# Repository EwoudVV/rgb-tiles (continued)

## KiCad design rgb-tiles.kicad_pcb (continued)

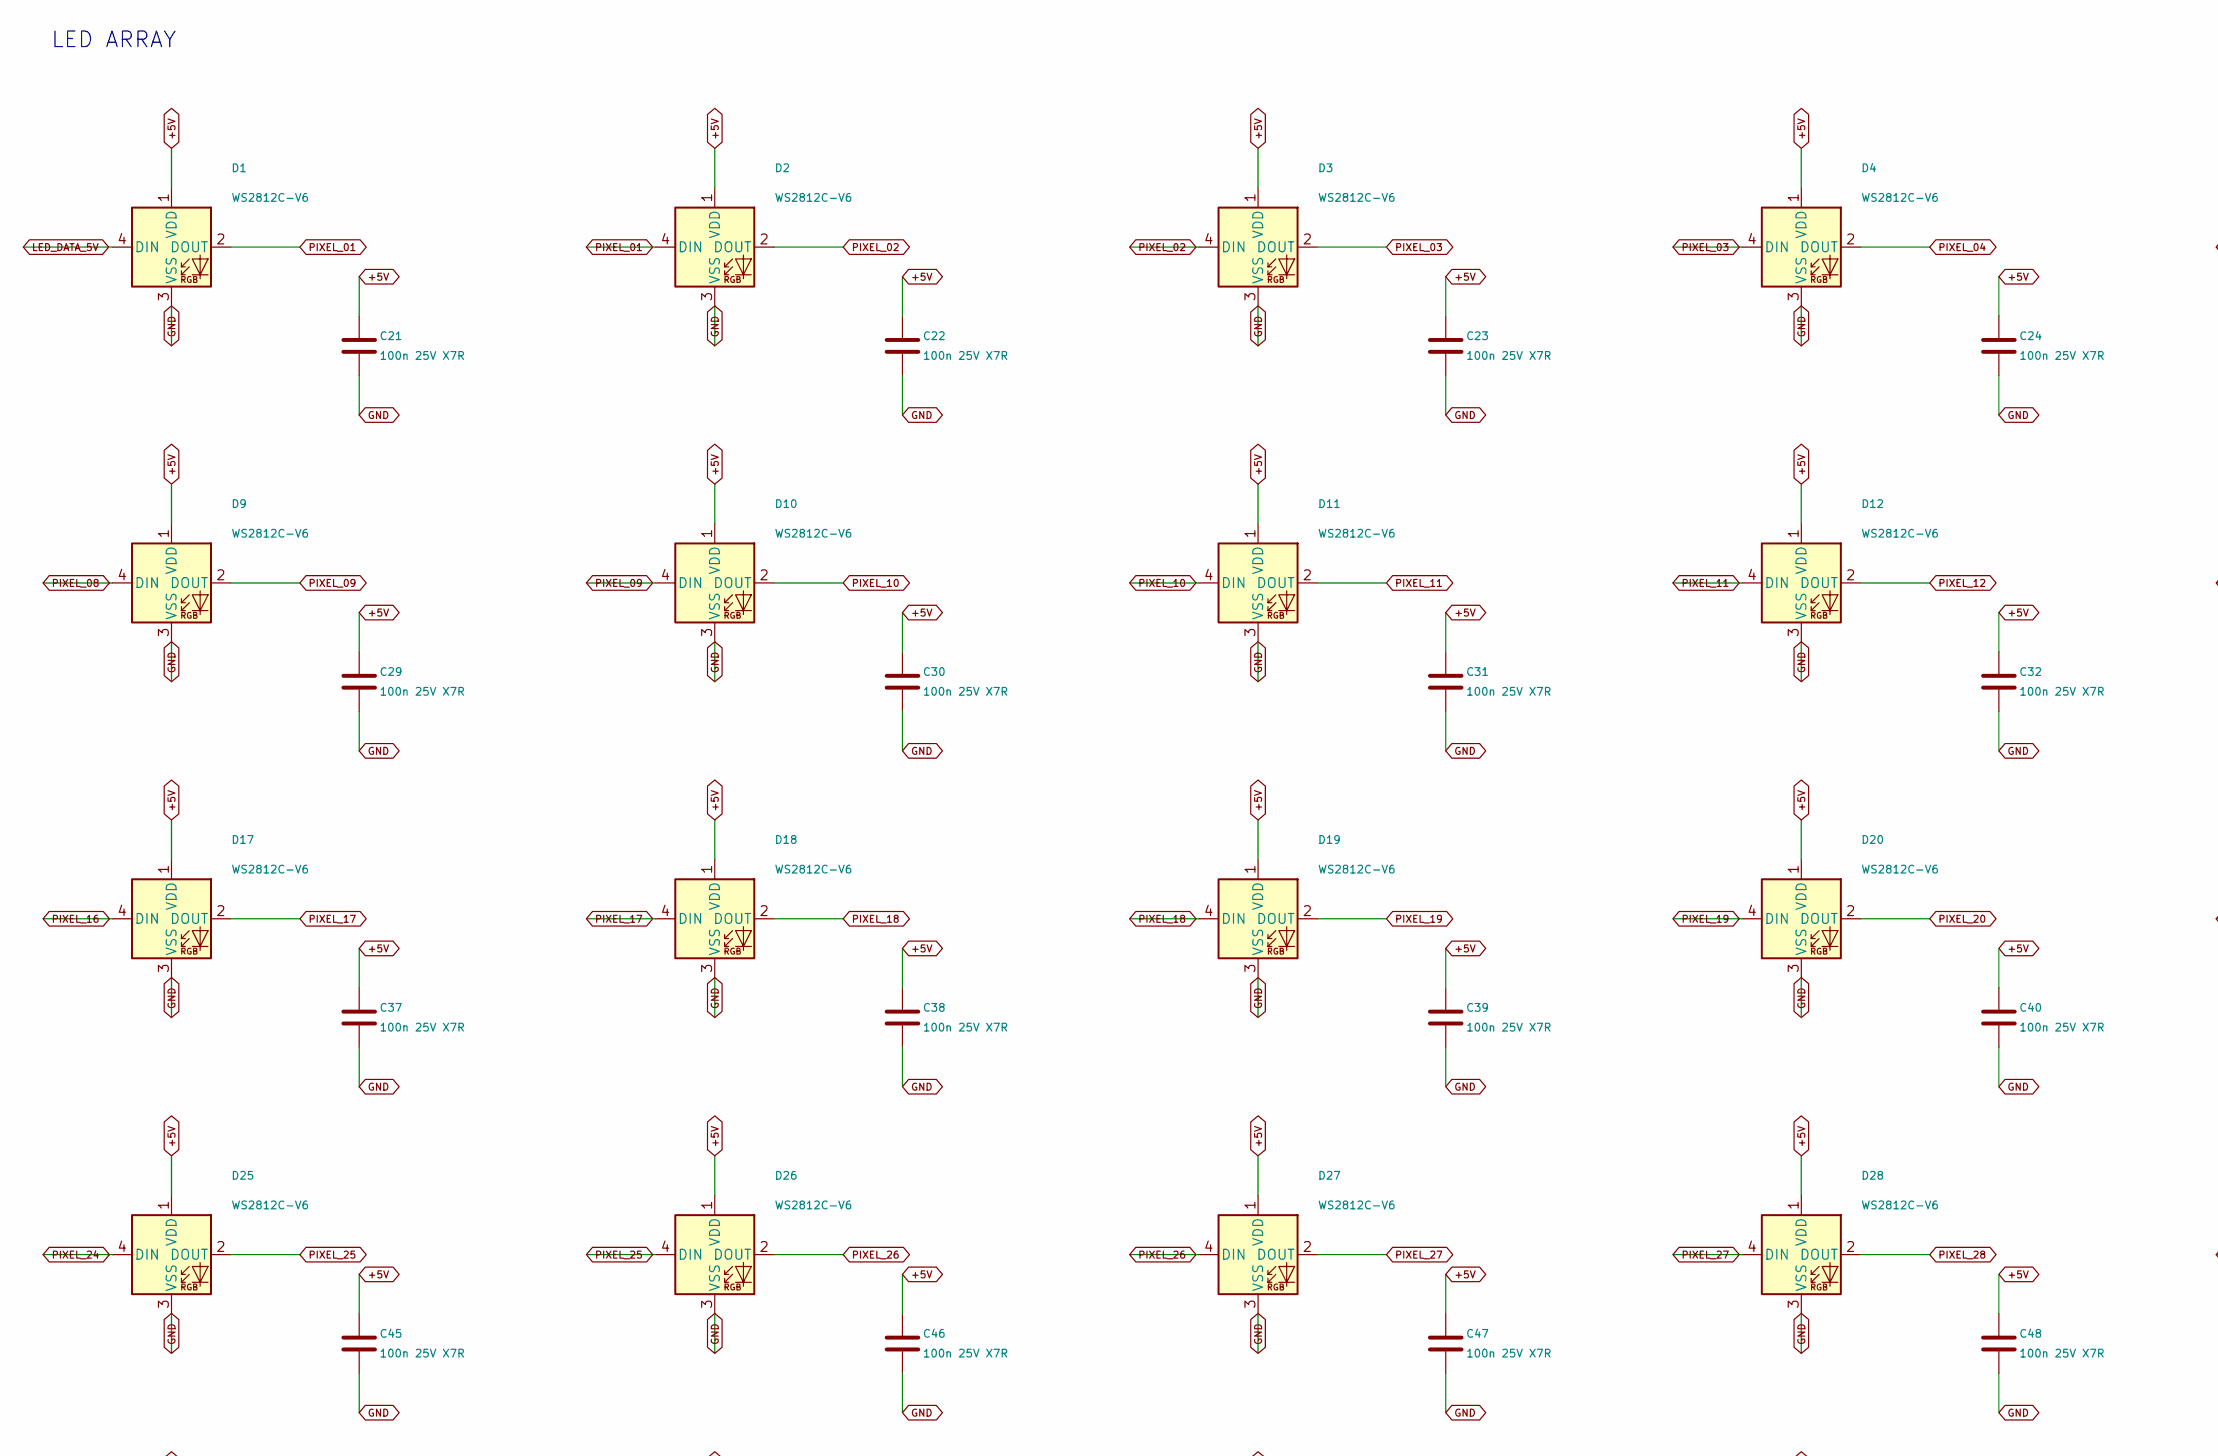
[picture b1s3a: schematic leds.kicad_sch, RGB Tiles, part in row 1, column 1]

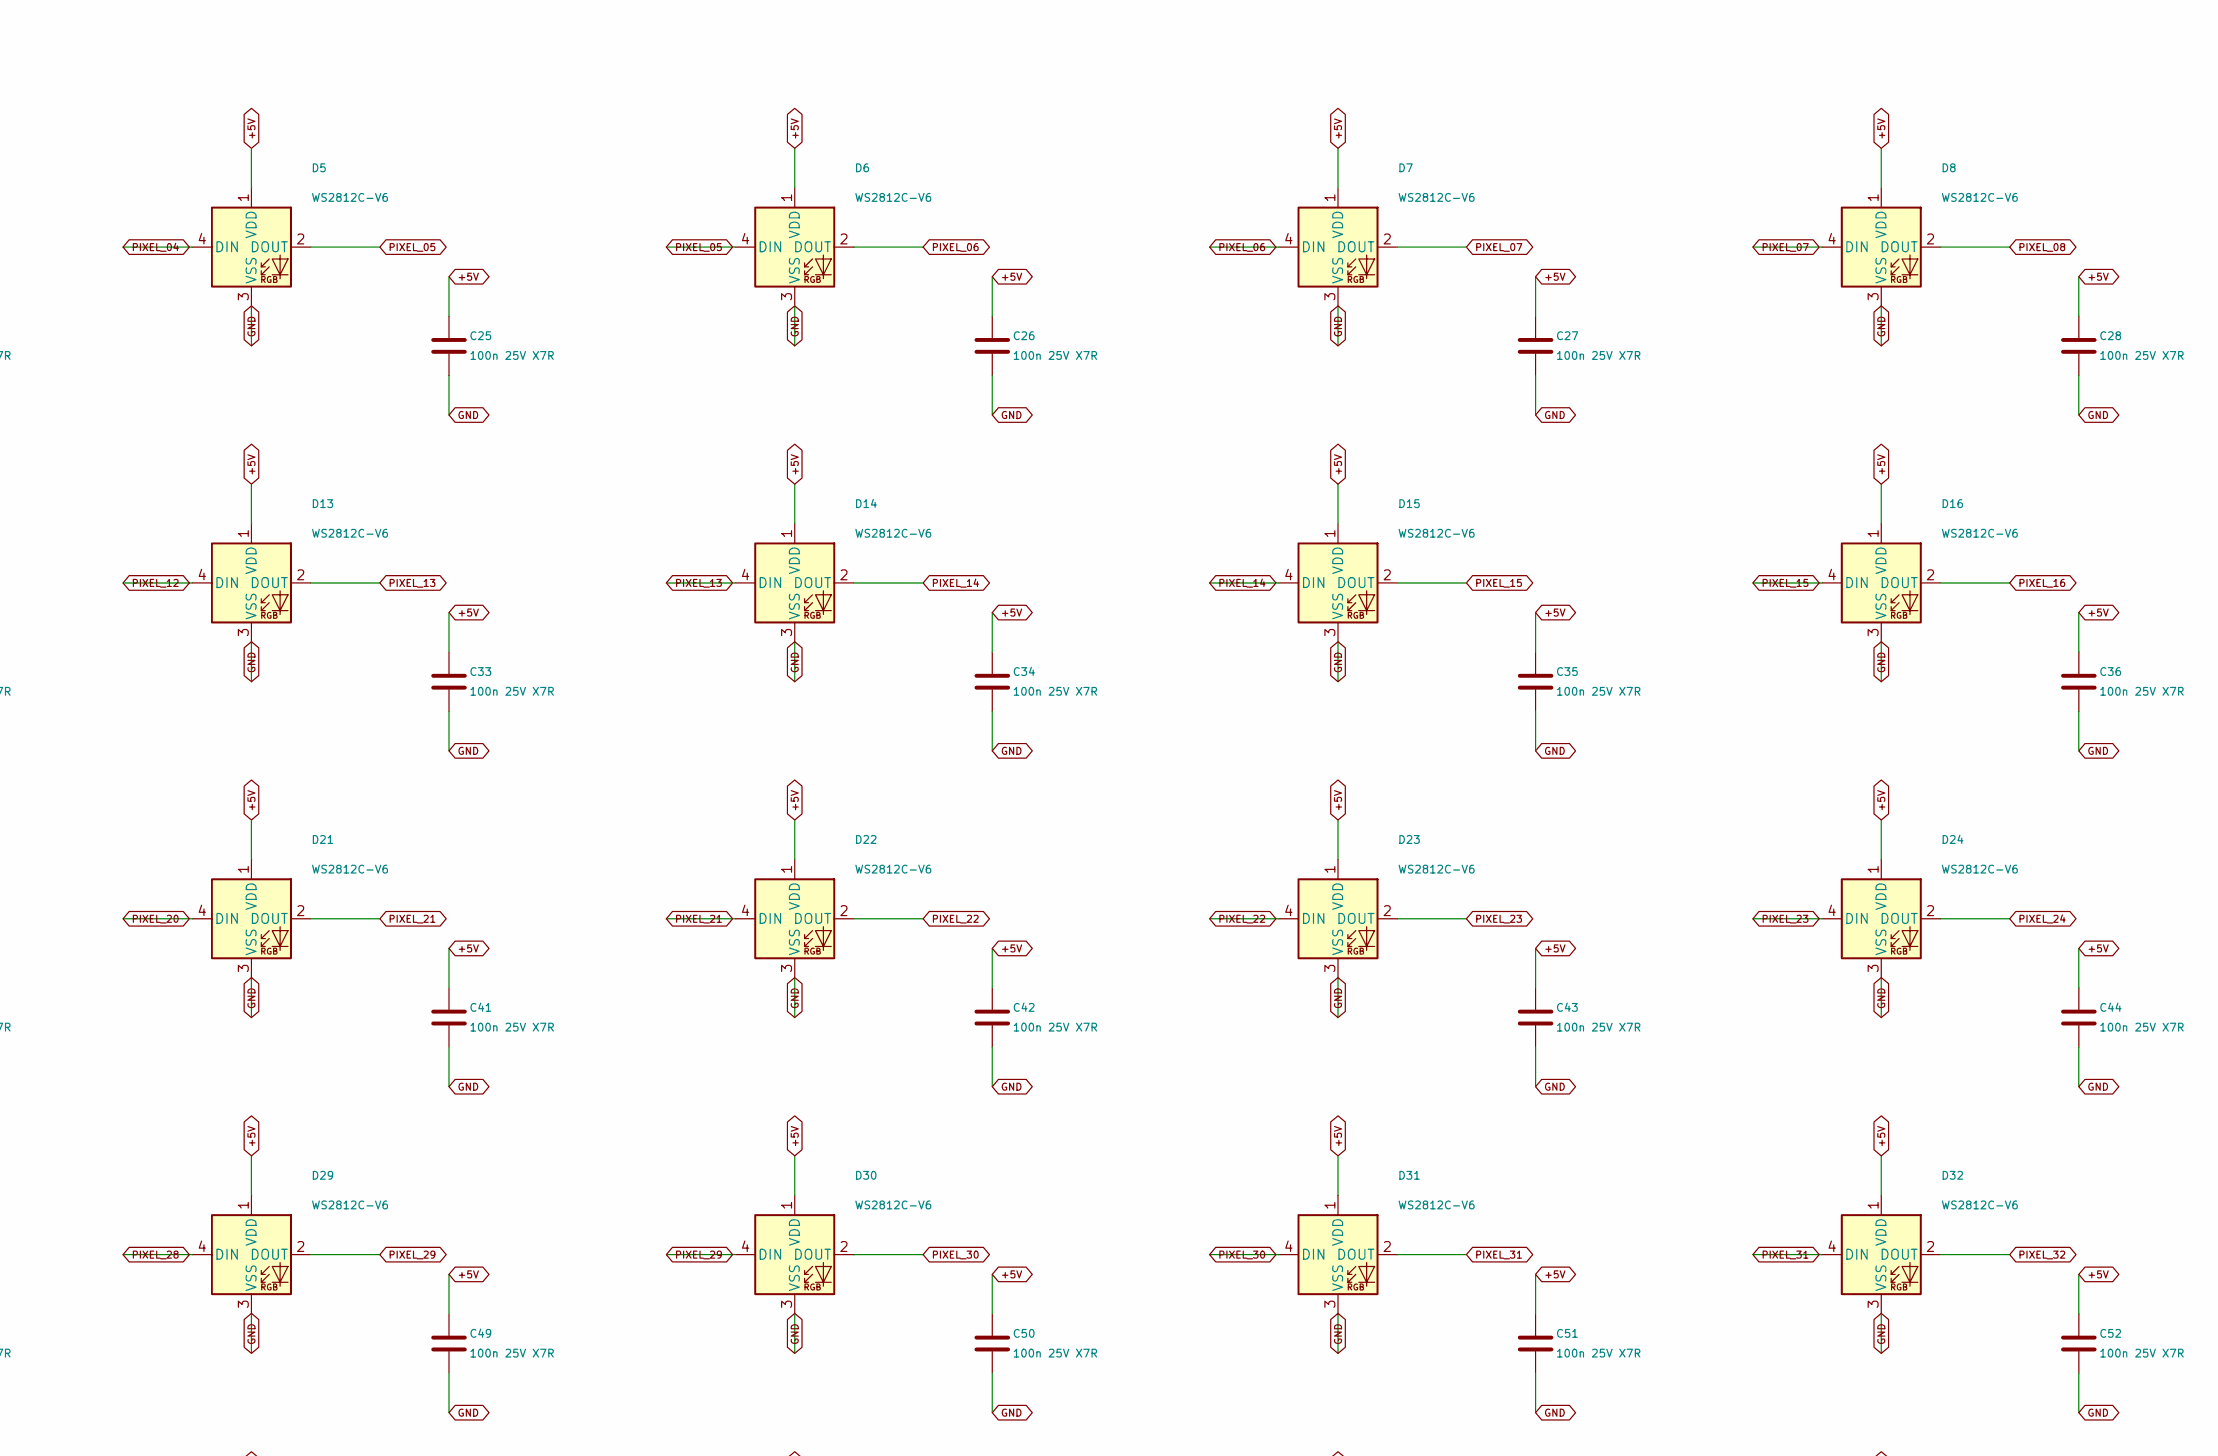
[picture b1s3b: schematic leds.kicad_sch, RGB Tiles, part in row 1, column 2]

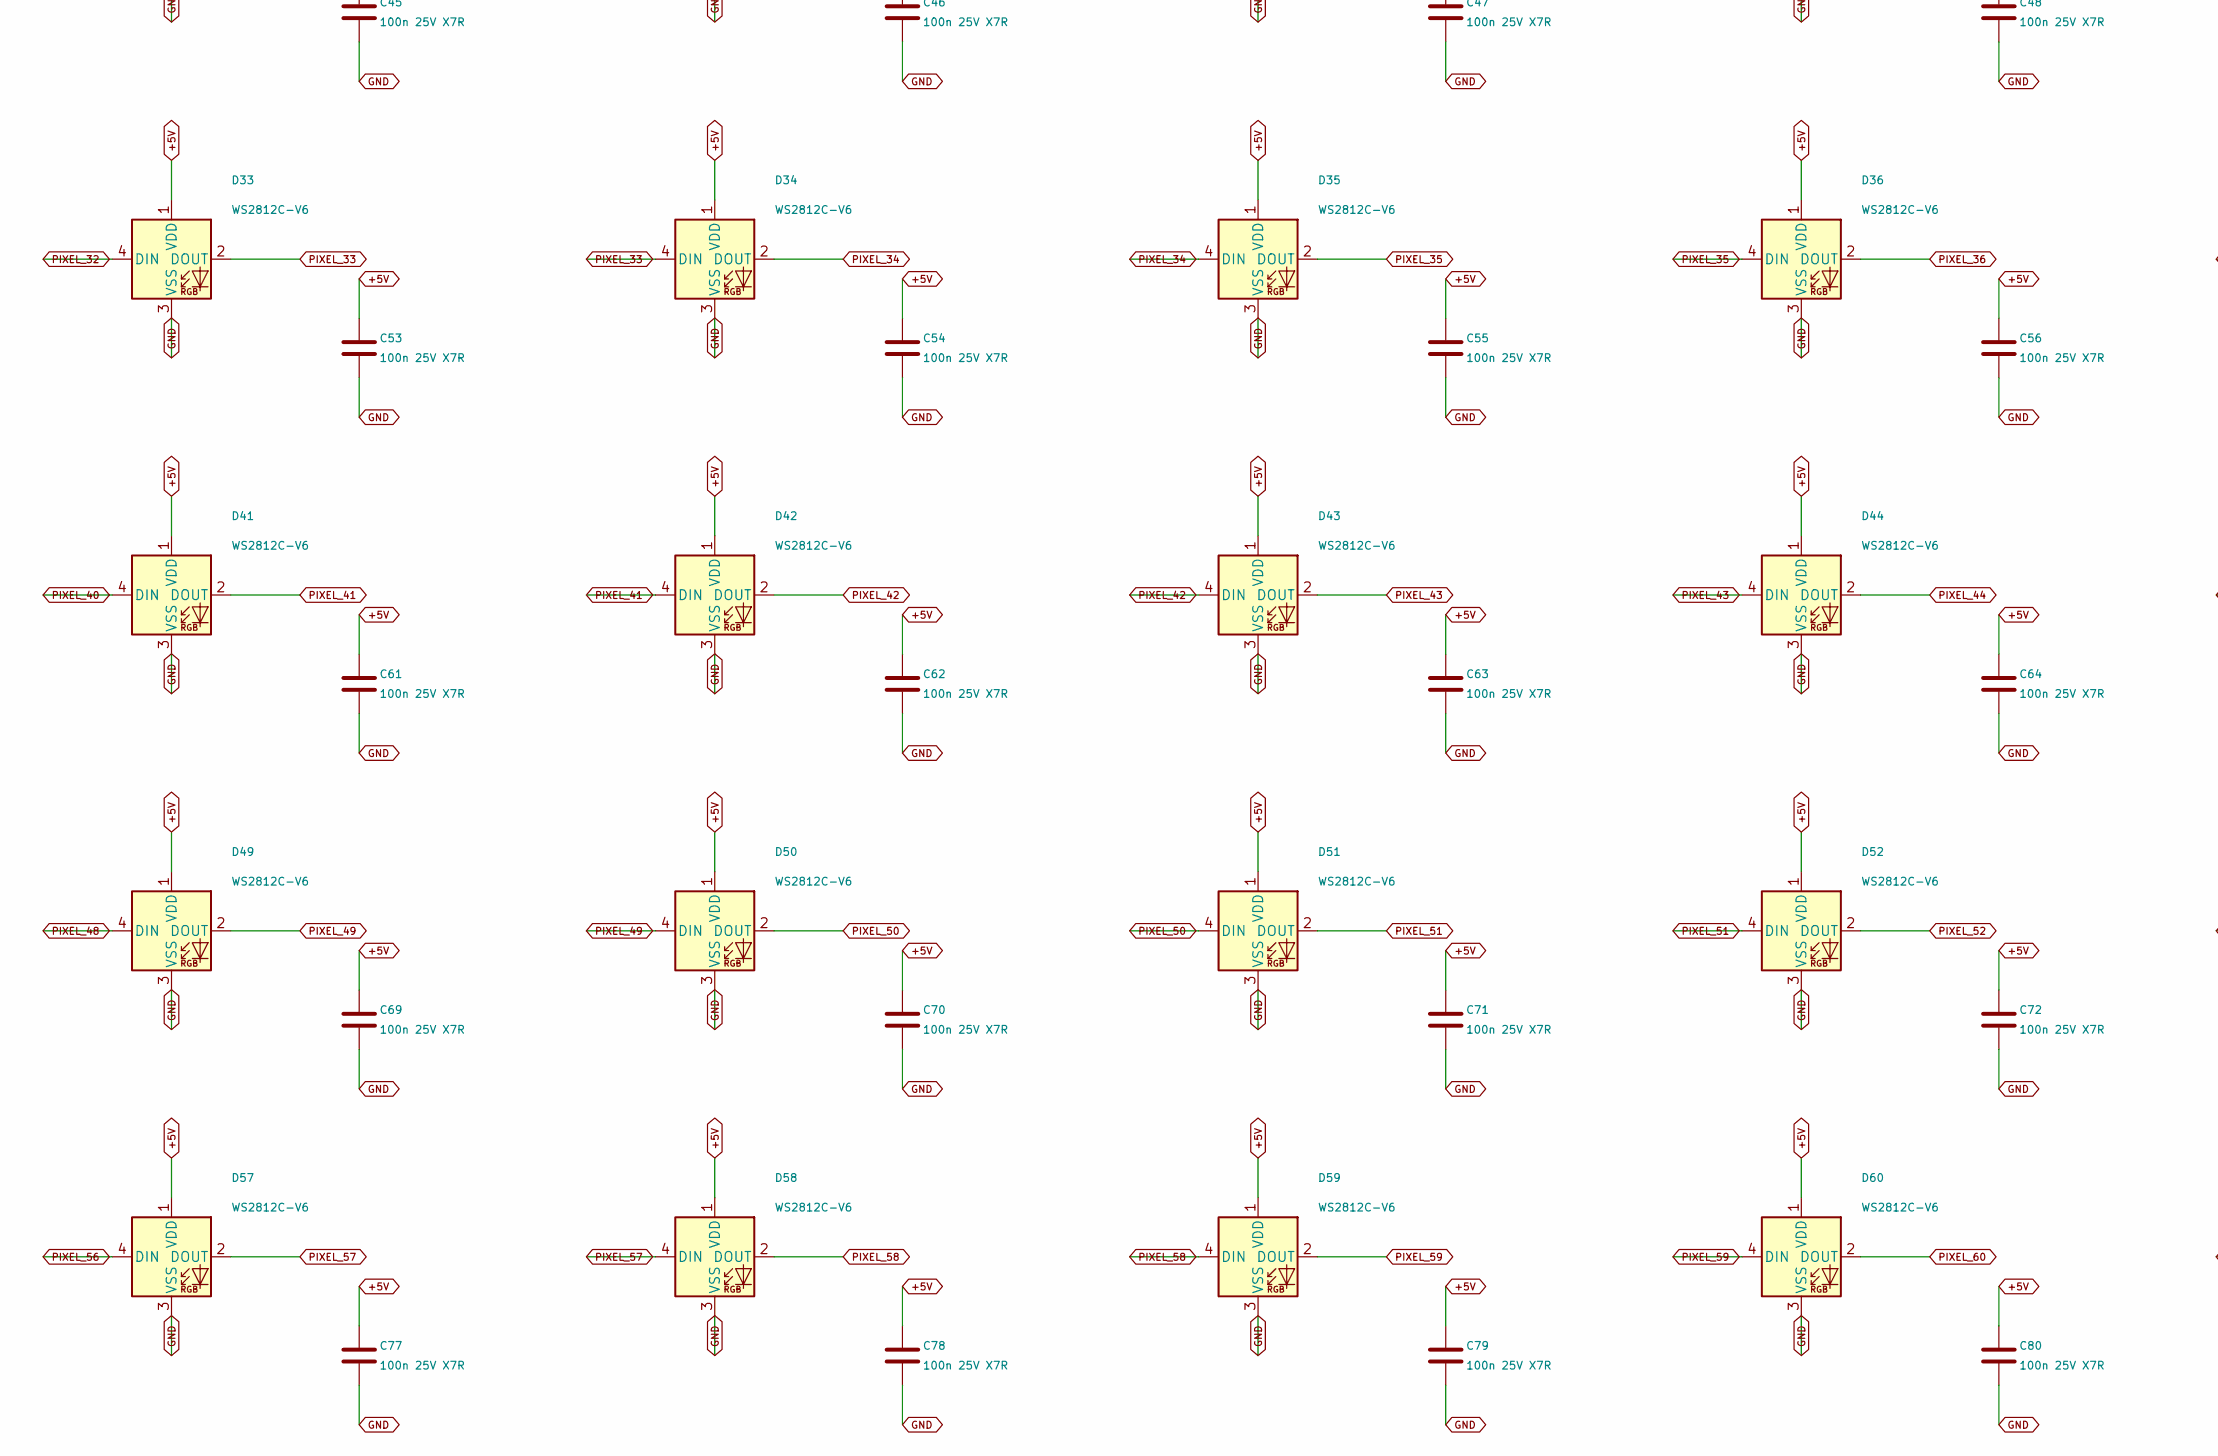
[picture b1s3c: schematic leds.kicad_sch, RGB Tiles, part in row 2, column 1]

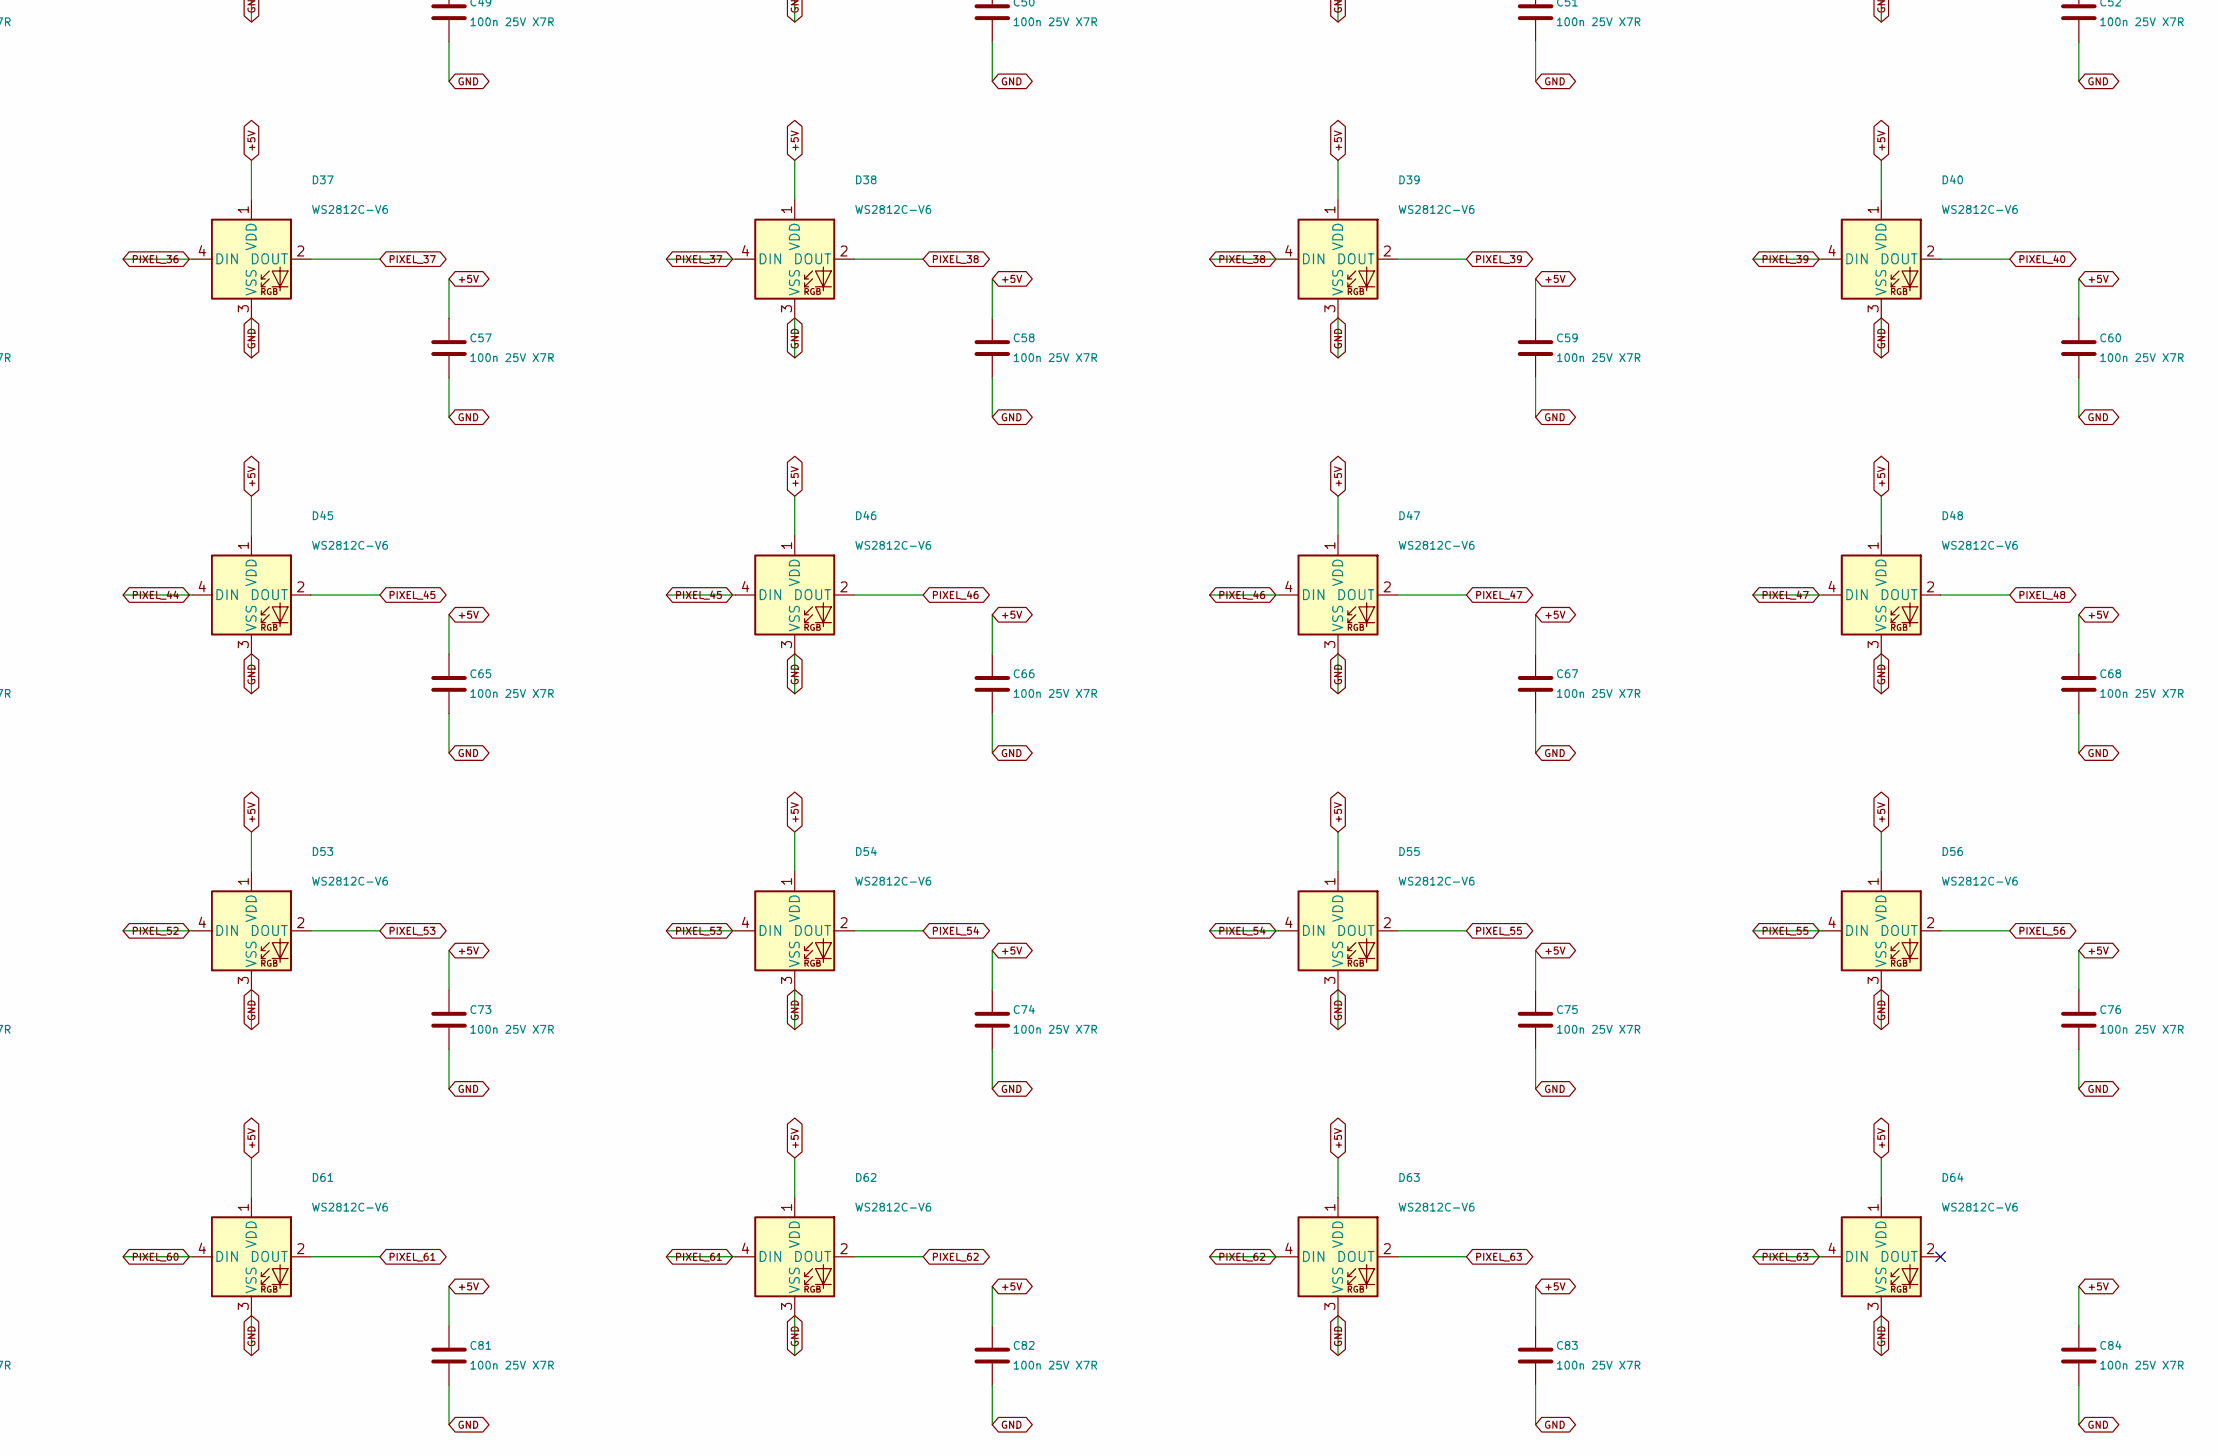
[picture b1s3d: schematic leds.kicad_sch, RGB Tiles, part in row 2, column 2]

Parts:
C21, C22, C23, C24, C25, C26, C27, C28, C29, C30, C31, C32, C33, C34, C35, C36, C37, C38, C39, C40, C41, C42, C43, C44, C45, C46, C47, C48, C49, C50, C51, C52, C53, C54, C55, C56, C57, C58, C59, C60, C61, C62, C63, C64, C65, C66, C67, C68, C69, C70, C71, C72, C73, C74, C75, C76, C77, C78, C79, C80, C81, C82, C83, C84: 100n 25V X7R; C_0603_1608Metric; MPN CL10B104KA8NNNC
D1, D2, D3, D4, D5, D6, D7, D8, D9, D10, D11, D12, D13, D14, D15, D16, D17, D18, D19, D20, D21, D22, D23, D24, D25, D26, D27, D28, D29, D30, D31, D32, D33, D34, D35, D36, D37, D38, D39, D40, D41, D42, D43, D44, D45, D46, D47, D48, D49, D50, D51, D52, D53, D54, D55, D56, D57, D58, D59, D60, D61, D62, D63, D64: WS2812C-V6; LED_WS2812C-V6_5050_SteppedCourtyard; MPN WS2812C-V6

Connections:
+5V: C21.1, C22.1, C23.1, C24.1, C25.1, C26.1, C27.1, C28.1, C29.1, C30.1, C31.1, C32.1, C33.1, C34.1, C35.1, C36.1, C37.1, C38.1, C39.1, C40.1, C41.1, C42.1, C43.1, C44.1, C45.1, C46.1, C47.1, C48.1, C49.1, C50.1, C51.1, C52.1, C53.1, C54.1, C55.1, C56.1, C57.1, C58.1, C59.1, C60.1, C61.1, C62.1, C63.1, C64.1, C65.1, C66.1, C67.1, C68.1, C69.1, C70.1, C71.1, C72.1, C73.1, C74.1, C75.1, C76.1, C77.1, C78.1, C79.1, C80.1, C81.1, C82.1, C83.1, C84.1, D1.1 (VDD), D2.1 (VDD), D3.1 (VDD), D4.1 (VDD), D5.1 (VDD), D6.1 (VDD), D7.1 (VDD), D8.1 (VDD), D9.1 (VDD), D10.1 (VDD), D11.1 (VDD), D12.1 (VDD), D13.1 (VDD), D14.1 (VDD), D15.1 (VDD), D16.1 (VDD), D17.1 (VDD), D18.1 (VDD), D19.1 (VDD), D20.1 (VDD), D21.1 (VDD), D22.1 (VDD), D23.1 (VDD), D24.1 (VDD), D25.1 (VDD), D26.1 (VDD), D27.1 (VDD), D28.1 (VDD), D29.1 (VDD), D30.1 (VDD), D31.1 (VDD), D32.1 (VDD), D33.1 (VDD), D34.1 (VDD), D35.1 (VDD), D36.1 (VDD), D37.1 (VDD), D38.1 (VDD), D39.1 (VDD), D40.1 (VDD), D41.1 (VDD), D42.1 (VDD), D43.1 (VDD), D44.1 (VDD), D45.1 (VDD), D46.1 (VDD), D47.1 (VDD), D48.1 (VDD), D49.1 (VDD), D50.1 (VDD), D51.1 (VDD), D52.1 (VDD), D53.1 (VDD), D54.1 (VDD), D55.1 (VDD), D56.1 (VDD), D57.1 (VDD), D58.1 (VDD), D59.1 (VDD), D60.1 (VDD), D61.1 (VDD), D62.1 (VDD), D63.1 (VDD), D64.1 (VDD); also elsewhere on the board
GND: C21.2, C22.2, C23.2, C24.2, C25.2, C26.2, C27.2, C28.2, C29.2, C30.2, C31.2, C32.2, C33.2, C34.2, C35.2, C36.2, C37.2, C38.2, C39.2, C40.2, C41.2, C42.2, C43.2, C44.2, C45.2, C46.2, C47.2, C48.2, C49.2, C50.2, C51.2, C52.2, C53.2, C54.2, C55.2, C56.2, C57.2, C58.2, C59.2, C60.2, C61.2, C62.2, C63.2, C64.2, C65.2, C66.2, C67.2, C68.2, C69.2, C70.2, C71.2, C72.2, C73.2, C74.2, C75.2, C76.2, C77.2, C78.2, C79.2, C80.2, C81.2, C82.2, C83.2, C84.2, D1.3 (VSS), D2.3 (VSS), D3.3 (VSS), D4.3 (VSS), D5.3 (VSS), D6.3 (VSS), D7.3 (VSS), D8.3 (VSS), D9.3 (VSS), D10.3 (VSS), D11.3 (VSS), D12.3 (VSS), D13.3 (VSS), D14.3 (VSS), D15.3 (VSS), D16.3 (VSS), D17.3 (VSS), D18.3 (VSS), D19.3 (VSS), D20.3 (VSS), D21.3 (VSS), D22.3 (VSS), D23.3 (VSS), D24.3 (VSS), D25.3 (VSS), D26.3 (VSS), D27.3 (VSS), D28.3 (VSS), D29.3 (VSS), D30.3 (VSS), D31.3 (VSS), D32.3 (VSS), D33.3 (VSS), D34.3 (VSS), D35.3 (VSS), D36.3 (VSS), D37.3 (VSS), D38.3 (VSS), D39.3 (VSS), D40.3 (VSS), D41.3 (VSS), D42.3 (VSS), D43.3 (VSS), D44.3 (VSS), D45.3 (VSS), D46.3 (VSS), D47.3 (VSS), D48.3 (VSS), D49.3 (VSS), D50.3 (VSS), D51.3 (VSS), D52.3 (VSS), D53.3 (VSS), D54.3 (VSS), D55.3 (VSS), D56.3 (VSS), D57.3 (VSS), D58.3 (VSS), D59.3 (VSS), D60.3 (VSS), D61.3 (VSS), D62.3 (VSS), D63.3 (VSS), D64.3 (VSS); also elsewhere on the board
LED_DATA_5V: D1.4 (DIN); also elsewhere on the board
PIXEL_01: D1.2 (DOUT), D2.4 (DIN)
PIXEL_02: D2.2 (DOUT), D3.4 (DIN)
PIXEL_03: D3.2 (DOUT), D4.4 (DIN)
PIXEL_04: D4.2 (DOUT), D5.4 (DIN)
PIXEL_05: D5.2 (DOUT), D6.4 (DIN)
PIXEL_06: D6.2 (DOUT), D7.4 (DIN)
PIXEL_07: D7.2 (DOUT), D8.4 (DIN)
PIXEL_08: D8.2 (DOUT), D9.4 (DIN)
PIXEL_09: D9.2 (DOUT), D10.4 (DIN)
PIXEL_10: D10.2 (DOUT), D11.4 (DIN)
PIXEL_11: D11.2 (DOUT), D12.4 (DIN)
PIXEL_12: D12.2 (DOUT), D13.4 (DIN)
PIXEL_13: D13.2 (DOUT), D14.4 (DIN)
PIXEL_14: D14.2 (DOUT), D15.4 (DIN)
PIXEL_15: D15.2 (DOUT), D16.4 (DIN)
PIXEL_16: D16.2 (DOUT), D17.4 (DIN)
PIXEL_17: D17.2 (DOUT), D18.4 (DIN)
PIXEL_18: D18.2 (DOUT), D19.4 (DIN)
PIXEL_19: D19.2 (DOUT), D20.4 (DIN)
PIXEL_20: D20.2 (DOUT), D21.4 (DIN)
PIXEL_21: D21.2 (DOUT), D22.4 (DIN)
PIXEL_22: D22.2 (DOUT), D23.4 (DIN)
PIXEL_23: D23.2 (DOUT), D24.4 (DIN)
PIXEL_24: D24.2 (DOUT), D25.4 (DIN)
PIXEL_25: D25.2 (DOUT), D26.4 (DIN)
PIXEL_26: D26.2 (DOUT), D27.4 (DIN)
PIXEL_27: D27.2 (DOUT), D28.4 (DIN)
PIXEL_28: D28.2 (DOUT), D29.4 (DIN)
PIXEL_29: D29.2 (DOUT), D30.4 (DIN)
PIXEL_30: D30.2 (DOUT), D31.4 (DIN)
PIXEL_31: D31.2 (DOUT), D32.4 (DIN)
PIXEL_32: D32.2 (DOUT), D33.4 (DIN)
PIXEL_33: D33.2 (DOUT), D34.4 (DIN)
PIXEL_34: D34.2 (DOUT), D35.4 (DIN)
PIXEL_35: D35.2 (DOUT), D36.4 (DIN)
PIXEL_36: D36.2 (DOUT), D37.4 (DIN)
PIXEL_37: D37.2 (DOUT), D38.4 (DIN)
PIXEL_38: D38.2 (DOUT), D39.4 (DIN)
PIXEL_39: D39.2 (DOUT), D40.4 (DIN)
PIXEL_40: D40.2 (DOUT), D41.4 (DIN)
PIXEL_41: D41.2 (DOUT), D42.4 (DIN)
PIXEL_42: D42.2 (DOUT), D43.4 (DIN)
PIXEL_43: D43.2 (DOUT), D44.4 (DIN)
PIXEL_44: D44.2 (DOUT), D45.4 (DIN)
PIXEL_45: D45.2 (DOUT), D46.4 (DIN)
PIXEL_46: D46.2 (DOUT), D47.4 (DIN)
PIXEL_47: D47.2 (DOUT), D48.4 (DIN)
PIXEL_48: D48.2 (DOUT), D49.4 (DIN)
PIXEL_49: D49.2 (DOUT), D50.4 (DIN)
PIXEL_50: D50.2 (DOUT), D51.4 (DIN)
PIXEL_51: D51.2 (DOUT), D52.4 (DIN)
PIXEL_52: D52.2 (DOUT), D53.4 (DIN)
PIXEL_53: D53.2 (DOUT), D54.4 (DIN)
PIXEL_54: D54.2 (DOUT), D55.4 (DIN)
PIXEL_55: D55.2 (DOUT), D56.4 (DIN)
PIXEL_56: D56.2 (DOUT), D57.4 (DIN)
PIXEL_57: D57.2 (DOUT), D58.4 (DIN)
PIXEL_58: D58.2 (DOUT), D59.4 (DIN)
PIXEL_59: D59.2 (DOUT), D60.4 (DIN)
PIXEL_60: D60.2 (DOUT), D61.4 (DIN)
PIXEL_61: D61.2 (DOUT), D62.4 (DIN)
PIXEL_62: D62.2 (DOUT), D63.4 (DIN)
PIXEL_63: D63.2 (DOUT), D64.4 (DIN)

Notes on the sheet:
LED ARRAY

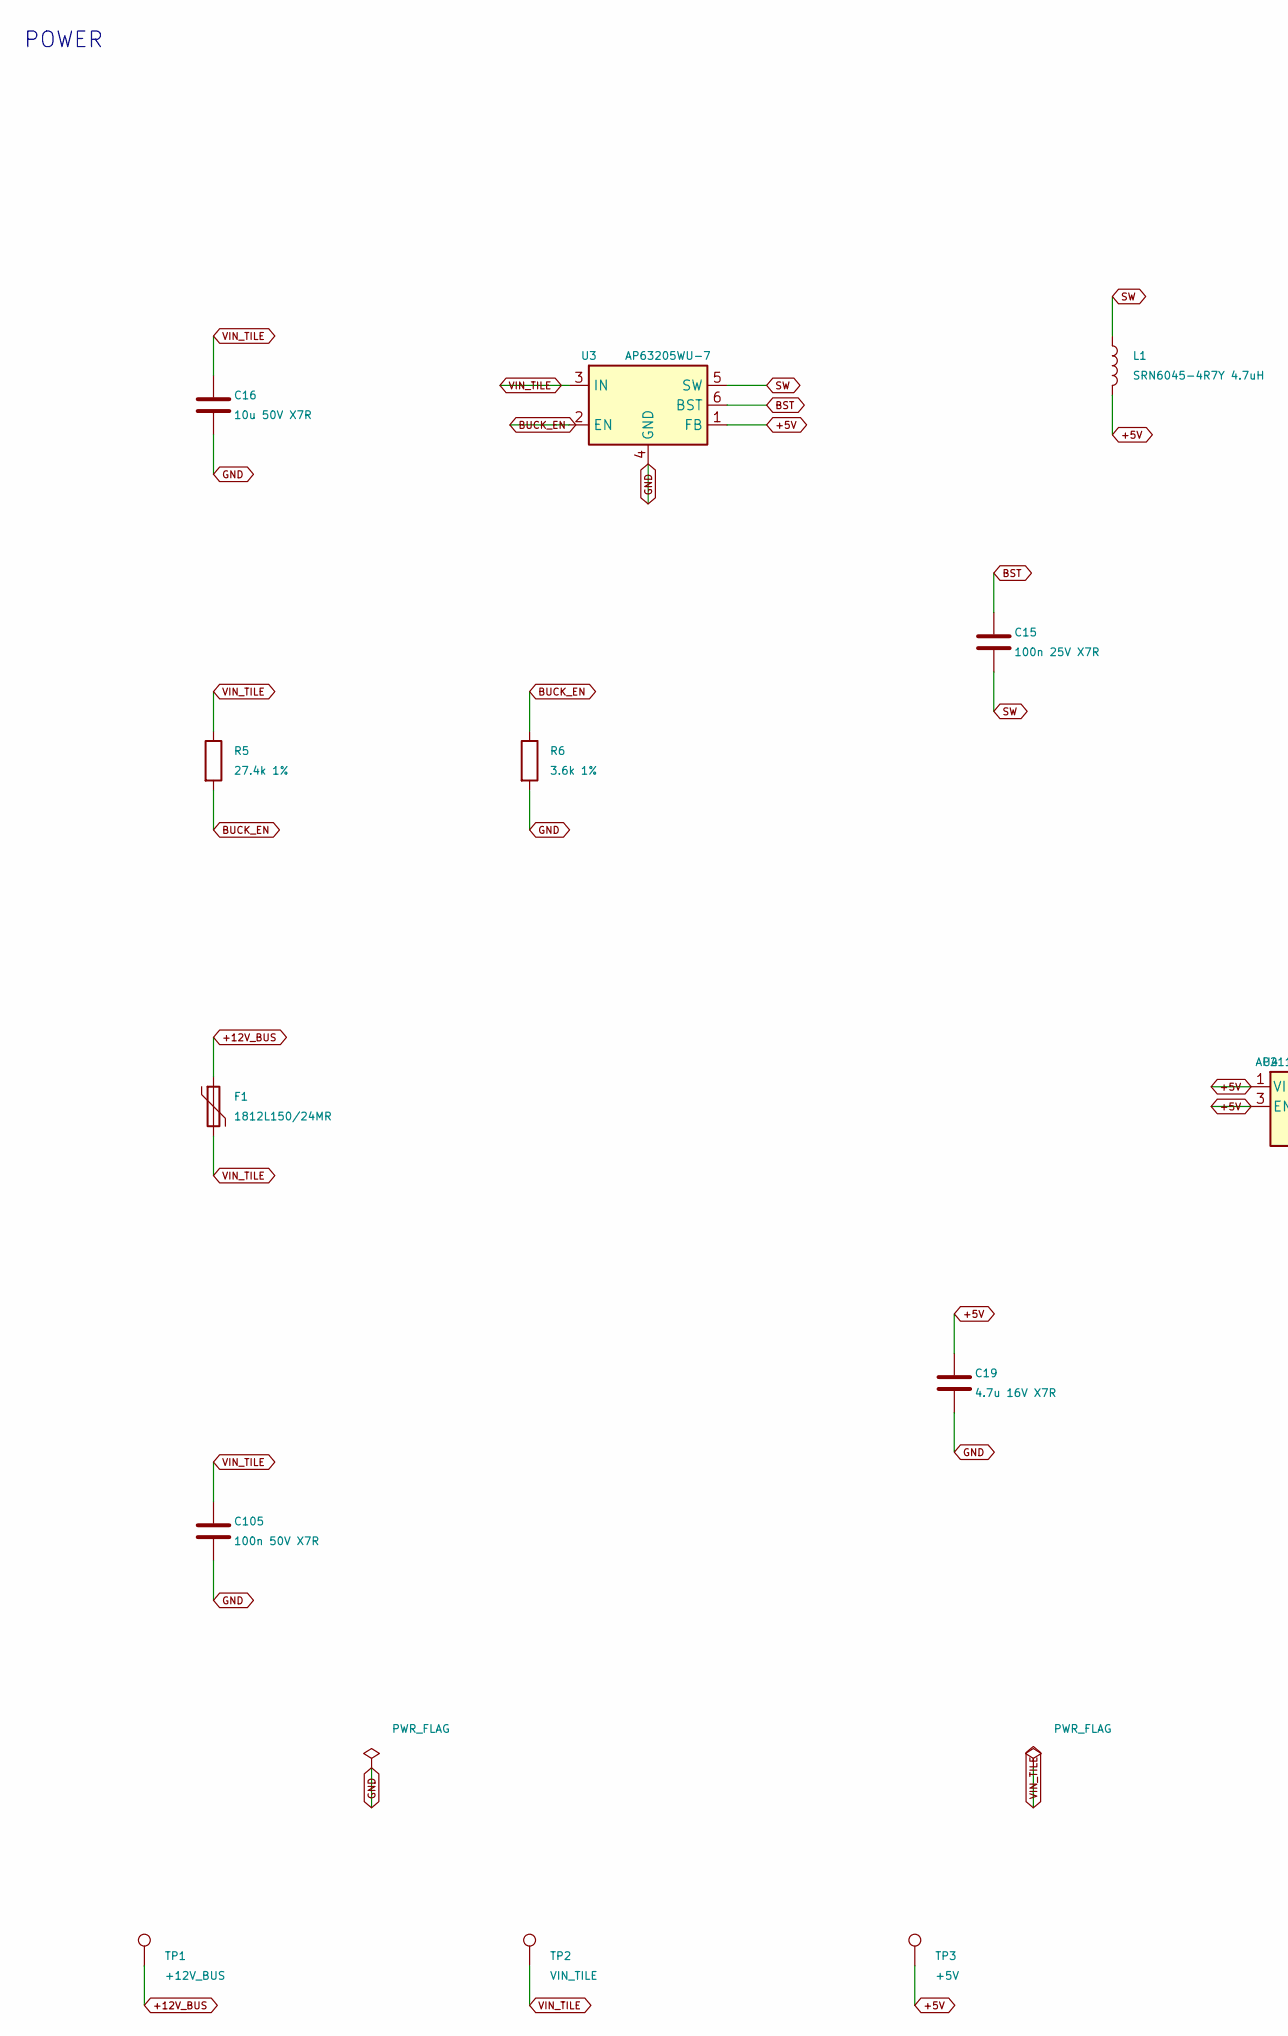
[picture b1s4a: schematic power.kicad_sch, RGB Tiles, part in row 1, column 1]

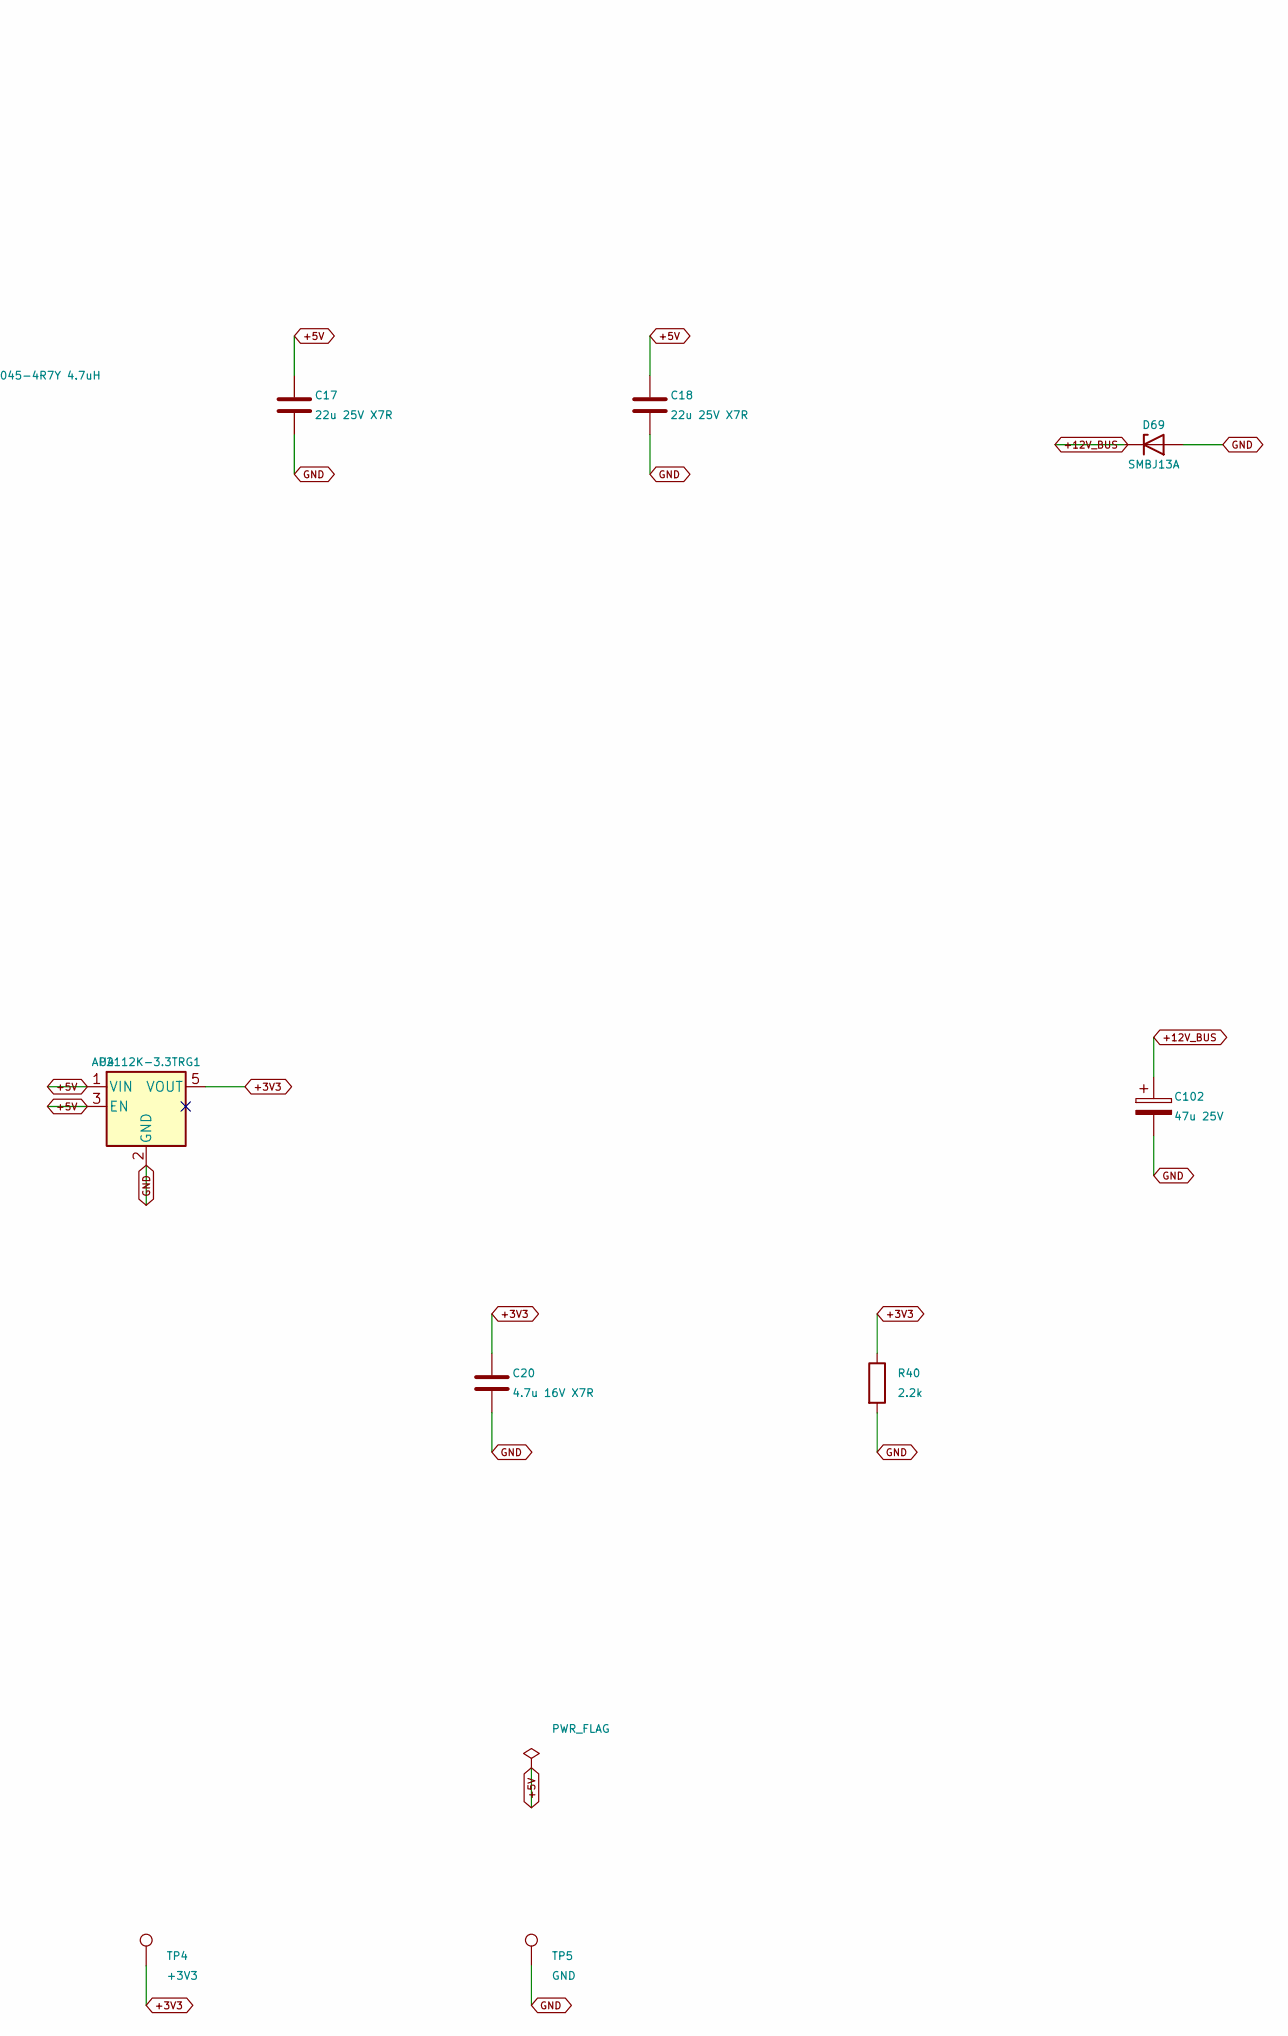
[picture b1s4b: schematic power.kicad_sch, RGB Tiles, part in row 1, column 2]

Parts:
C15: 100n 25V X7R; C_0603_1608Metric; MPN CL10B104KA8NNNC
C16: 10u 50V X7R; C_1210_3225Metric; MPN CL32B106KBJNNNE
C17, C18: 22u 25V X7R; C_1210_3225Metric; MPN CL32B226KAJNNNE
C19, C20: 4.7u 16V X7R; C_0805_2012Metric; MPN C0805C475K4RACTU
C102: 47u 25V; CP_Elec_5x5.8; MPN EEEFT1E470AR
C105: 100n 50V X7R; C_0603_1608Metric; MPN C0603C104K5RACTU
D69: SMBJ13A; D_SMB; MPN SMBJ13A-13-F
F1: 1812L150/24MR; Fuse_1812_4532Metric; MPN 1812L150/24MR
L1: SRN6045-4R7Y 4.7uH; L_Bourns_SRN6045; MPN SRN6045-4R7Y
R5: 27.4k 1%; R_0603_1608Metric; Tolerance 1%; MPN RC0603FR-0727K4L
R6: 3.6k 1%; R_0603_1608Metric; Tolerance 1%; MPN RC0603FR-133K6L
R40: 2.2k; R_0603_1608Metric; Tolerance 1%; MPN RC0603FR-072K2L
TP1: +12V_BUS; TestPoint_Pad_D1.5mm
TP2: VIN_TILE; TestPoint_Pad_D1.5mm
TP3: +5V; TestPoint_Pad_D1.5mm
TP4: +3V3; TestPoint_Pad_D1.5mm
TP5: GND; TestPoint_Pad_D1.5mm
U3: AP63205WU-7; TSOT-23-6; MPN AP63205WU-7
U4: AP2112K-3.3TRG1; SOT-23-5; MPN AP2112K-3.3TRG1

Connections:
+3V3: C20.1, R40.1, TP4.1, U4.5 (VOUT); also elsewhere on the board
+5V: C17.1, C18.1, C19.1, L1.2, TP3.1, U3.1 (FB), U4.1 (VIN), U4.3 (EN); also elsewhere on the board
+12V_BUS: C102.1, D69.1 (K), F1.1, TP1.1; also elsewhere on the board
BST: C15.1, U3.6 (BST)
BUCK_EN: R5.2, R6.1, U3.2 (EN)
GND: C16.2, C17.2, C18.2, C19.2, C20.2, C102.2, C105.2, D69.2 (A), R6.2, R40.2, TP5.1, U3.4 (GND), U4.2 (GND); also elsewhere on the board
SW: C15.2, L1.1, U3.5 (SW)
VIN_TILE: C16.1, C105.1, F1.2, R5.1, TP2.1, U3.3 (IN)

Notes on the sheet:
POWER
